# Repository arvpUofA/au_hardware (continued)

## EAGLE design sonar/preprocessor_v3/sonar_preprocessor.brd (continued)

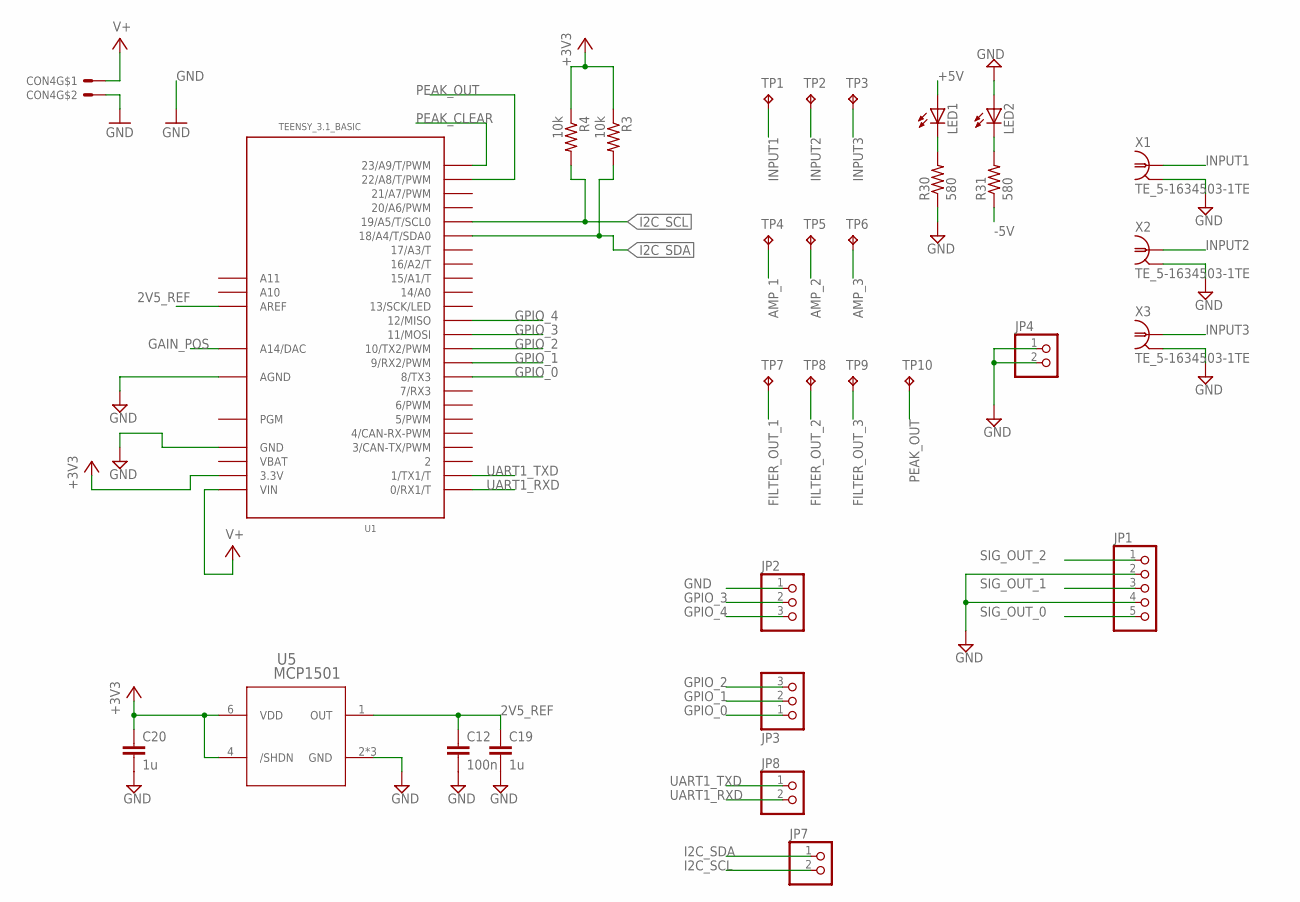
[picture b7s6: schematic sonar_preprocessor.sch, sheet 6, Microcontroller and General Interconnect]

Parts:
C12: 100n; C0805
C19, C20: 1u; C0805
CON4: MOLEX_5566-2; 5566-2
JP1: PINHD-1X5/90; 1X05/90
JP2, JP3: PINHD-1X03_2.54-SMD-90°; 1X03SMD/90
JP4, JP7: PINHD-1X2; 1X02
JP8: PINHD-1X02_2.54-SMD-90°; 1X02SMD/90
LED1, LED2: LEDSML0805; SML0805
R3, R4: 10k; R0805
R30, R31: 580; R0805
TP1, TP2, TP3, TP4, TP5, TP6, TP7, TP8, TP9, TP10: TPB2,54; B2,54
U1: TEENSY_3.1_BASIC
U5: MCP1501; SOT23-6
X1, X2, X3: TE_5-1634503-1TE; TE_5-1634503-1

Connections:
2V5_REF: C12.1, C19.1, U1.AREF, U5.1 (OUT)
+3V3: C20.1, R3.1, R4.1, U1.3.3V, U1.3.3V1 (3.3V), U5.4 (/SHDN), U5.6 (VDD); also elsewhere on the board
+5V: LED1.A; also elsewhere on the board
-5V: R31.1; also elsewhere on the board
AMP_1: TP4.TP; also elsewhere on the board
AMP_2: TP5.TP; also elsewhere on the board
AMP_3: TP6.TP; also elsewhere on the board
FILTER_OUT_1: TP7.TP; also elsewhere on the board
FILTER_OUT_2: TP8.TP; also elsewhere on the board
FILTER_OUT_3: TP9.TP; also elsewhere on the board
GAIN_POS: U1.A14 (A14/DAC); also elsewhere on the board
GND: C12.2, C19.2, C20.2, CON4.2, JP1.2, JP1.4, JP2.1, JP4.1, JP4.2, LED2.A, R30.1, U1.AGND, U1.GND, U1.GND1 (GND), U5.2 (GND), U5.3 (GND), U5.5 (GND), X1.2, X1.3 (2), X1.4 (2), X1.5 (2), X2.2, X2.3 (2), X2.4 (2), X2.5 (2), X3.2, X3.3 (2), X3.4 (2), X3.5 (2); also elsewhere on the board
GPIO_0: JP3.1, U1.8 (8/TX3)
GPIO_1: JP3.2, U1.9 (9/RX2/PWM)
GPIO_2: JP3.3, U1.10 (10/TX2/PWM)
GPIO_3: JP2.2, U1.11 (11/MOSI)
GPIO_4: JP2.3, U1.12 (12/MISO)
I2C_SCL: JP7.2, R4.2, U1.19/A5 (19/A5/T/SCL0); also elsewhere on the board
I2C_SDA: JP7.1, R3.2, U1.18/A4 (18/A4/T/SDA0); also elsewhere on the board
INPUT1: TP1.TP, X1.1; also elsewhere on the board
INPUT2: TP2.TP, X2.1; also elsewhere on the board
INPUT3: TP3.TP, X3.1; also elsewhere on the board
unnamed: LED2.C, R31.2
unnamed: LED1.C, R30.2
PEAK_CLEAR: U1.23/A9 (23/A9/T/PWM); also elsewhere on the board
PEAK_OUT: TP10.TP, U1.22/A8 (22/A8/T/PWM); also elsewhere on the board
SIG_OUT_0: JP1.5; also elsewhere on the board
SIG_OUT_1: JP1.3; also elsewhere on the board
SIG_OUT_2: JP1.1; also elsewhere on the board
UART1_RXD: JP8.2, U1.0 (0/RX1/T)
UART1_TXD: JP8.1, U1.1 (1/TX1/T)
V+: CON4.1, U1.VIN; also elsewhere on the board
VBAT: U1.VBAT

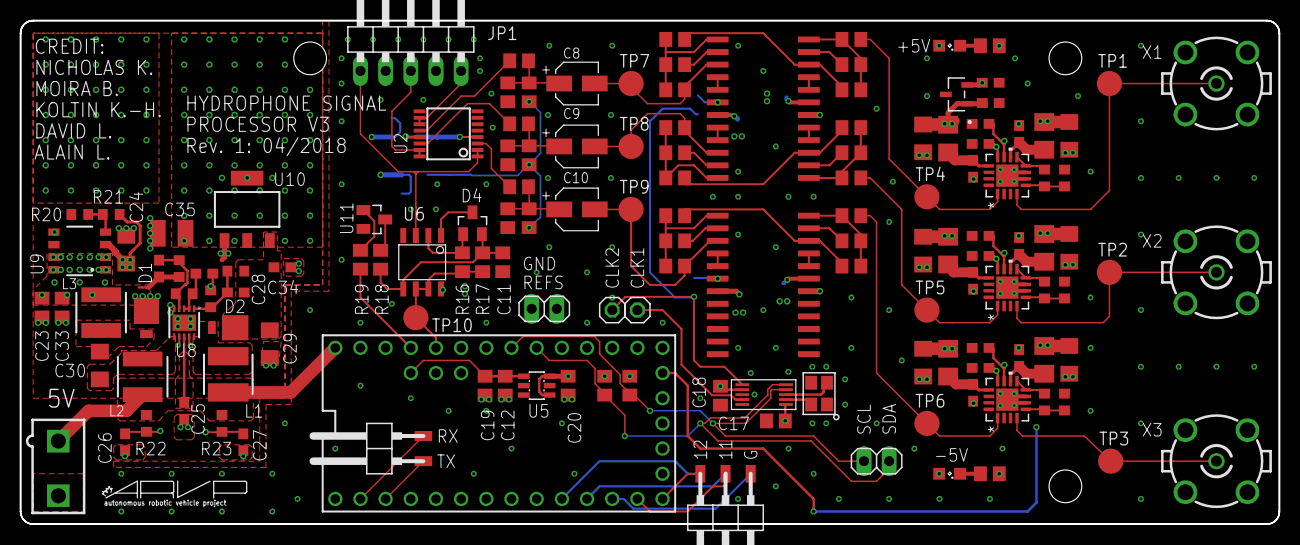
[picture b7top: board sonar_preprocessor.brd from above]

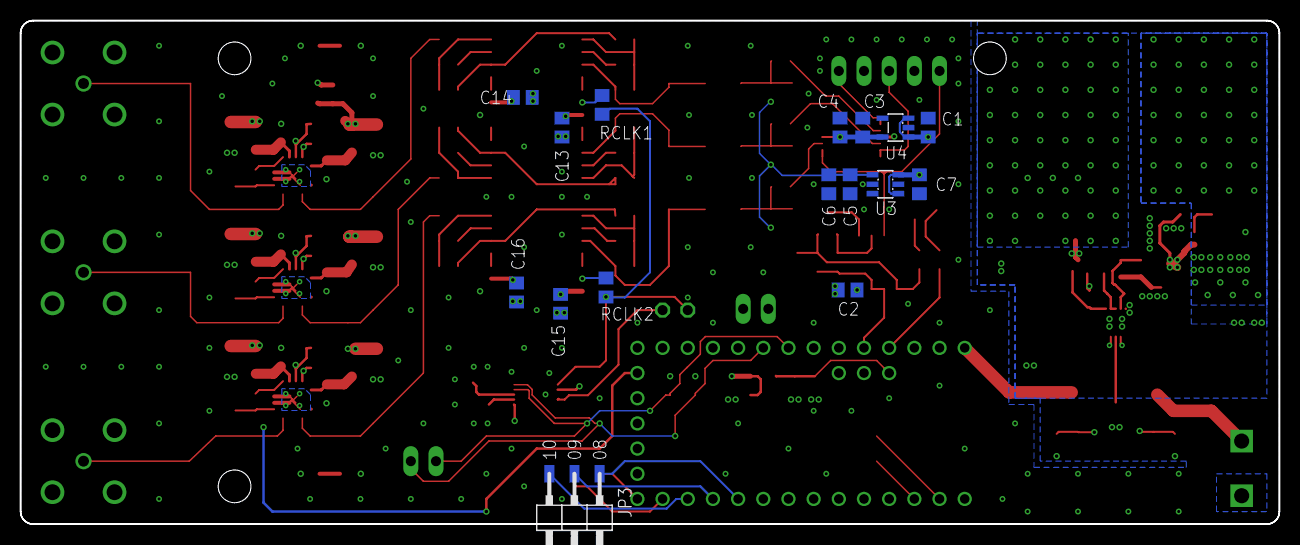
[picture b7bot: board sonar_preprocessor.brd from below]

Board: 4 copper layers, 127.0 x 50.8 mm, 163 parts (16 on the bottom side), 96 nets.

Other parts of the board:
U$1: A4L-LOC
U$2, U$3, U$5: STAND-OFF
U$4: ARVP

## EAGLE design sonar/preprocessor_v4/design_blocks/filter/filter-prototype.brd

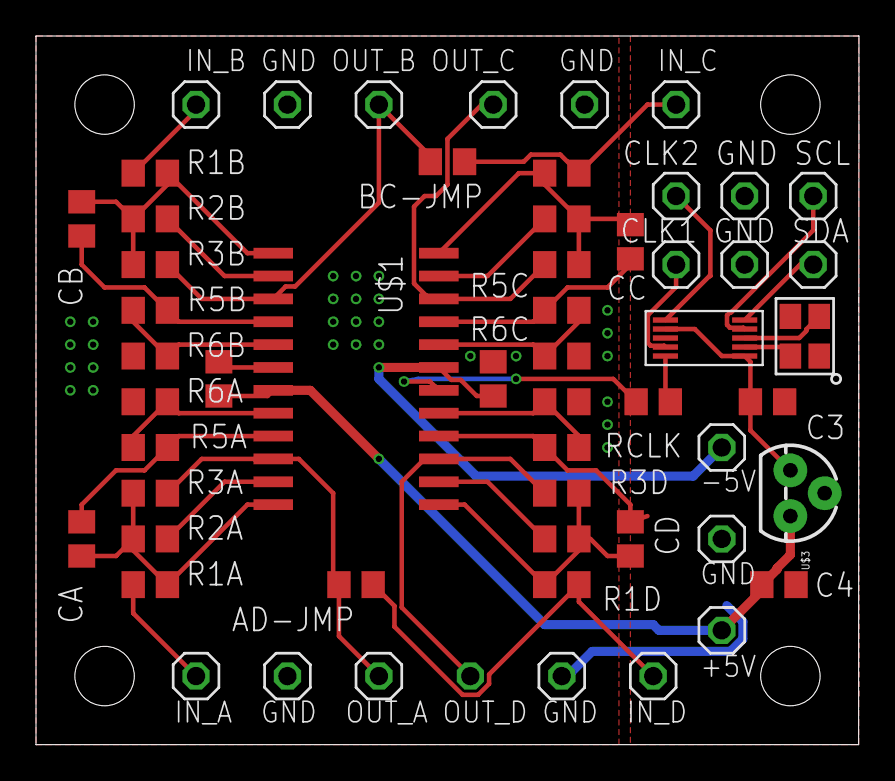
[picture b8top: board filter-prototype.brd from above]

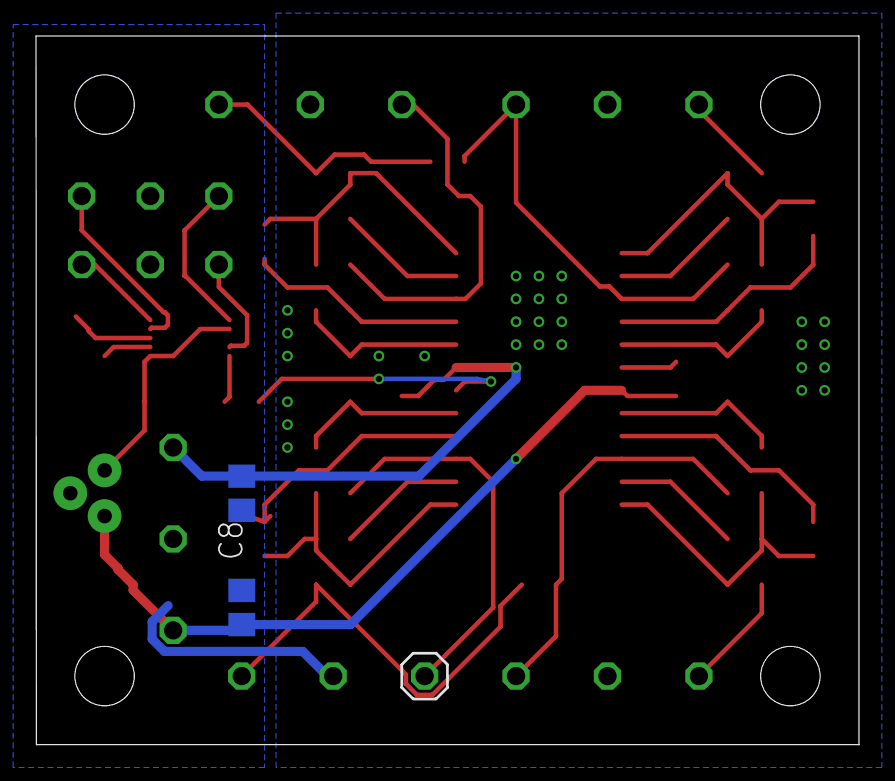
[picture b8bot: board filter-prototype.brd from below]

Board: 2 copper layers, 45.7 x 39.4 mm, 62 parts (3 on the bottom side), 36 nets.

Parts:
25MHZ: FA-238
AD-JMP: NOPOP; R0805
BC-JMP: NOPOP; R0805
C1, C2: 0.1u; C0805
C3: 0.47u; C0805
C4: 0.33u; C0805
C7, C8: 4.7u; C0805
CA: C0805
CB: C0805
CC: C0805
CD: C0805
JP1, JP2, JP3, JP4, JP5, JP6, JP7, JP9, JP10, JP11, JP12, JP13, JP14, JP15, JP16, JP17, JP18, JP19, JP20, JP21, JP22: 1X01
R1A, R3A: 350k; R0805
R1B, R3B: 300k; R0805
R1C: 94k; R0805
R1D, R3D: 225k; R0805
R2A, R2B: 10k; R0805
R2C: 7.5k; R0805
R2D, R5B, R6B: 5k; R0805
R3C: 187k; R0805
R5A, R5C, R5D: 0; R0805
R6A, R6C, R6D: NOPOP; R0805
RCLK: 200; R0805
U$1: LTC1264SMD; SO24W
U$2: SI5351A; MSOP-10
U$3: L78L33ACZ; TO-92
U$4, U$5, U$6, U$25: STAND-OFF

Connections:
3V3: C3.1, U$2.P$1, U$2.P$7, U$3.1
+5V: C1.1, C4.1, C7.1, JP3.1, U$1.7, U$3.3
-5V: C2.1, C8.2, JP5.1, U$1.19
CLK1: JP13.1, U$2.P$9
CLK2: JP12.1, U$2.P$6
GND: 25MHZ.P$1, 25MHZ.P$3, C1.2, C2.2, C3.2, C4.2, C7.2, C8.1, JP2.1, JP4.1, JP14.1, JP17.1, JP20.1, JP21.1, JP22.1, R6A.1, R6B.1, R6C.1, R6D.2, U$1.6, U$2.P$8, U$3.2
IN_A: JP1.1, R1A.1
IN_B: JP6.1, R1B.1
IN_C: BC-JMP.2, JP7.1, R1C.1
IN_D: AD-JMP.2, JP9.1, R1D.2
unnamed: R2B.2, U$1.2
unnamed: RCLK.2, U$2.P$10
unnamed: R2C.2, U$1.23
unnamed: CB.2, R5B.1, U$1.4
unnamed: R5B.2, R6B.2, U$1.5
unnamed: CC.2, R5C.1, U$1.21
unnamed: R5C.2, R6C.2, U$1.20
unnamed: R2A.2, U$1.11
unnamed: CA.1, R5A.1, U$1.9
unnamed: R5A.2, R6A.2, U$1.8
unnamed: CB.1, R1B.2, R2B.1, R3B.1, U$1.1
unnamed: CC.1, R1C.2, R2C.1, R3C.1, U$1.24
unnamed: R5D.1, R6D.1, U$1.17
unnamed: CD.1, R5D.2, U$1.16
unnamed: R2D.1, U$1.14
unnamed: CD.2, R1D.1, R2D.2, R3D.2, U$1.13
unnamed: 25MHZ.P$4, U$2.P$2
unnamed: 25MHZ.P$2, U$2.P$3
unnamed: RCLK.1, U$1.18
unnamed: CA.2, R1A.2, R2A.1, R3A.1, U$1.12
OUT_A: AD-JMP.1, JP18.1, R3A.2, U$1.10
OUT_B: BC-JMP.1, JP19.1, R3B.2, U$1.3
OUT_C: JP15.1, R3C.2, U$1.22
OUT_D: JP16.1, R3D.1, U$1.15
SCL: JP11.1, U$2.P$4
SDA: JP10.1, U$2.P$5
